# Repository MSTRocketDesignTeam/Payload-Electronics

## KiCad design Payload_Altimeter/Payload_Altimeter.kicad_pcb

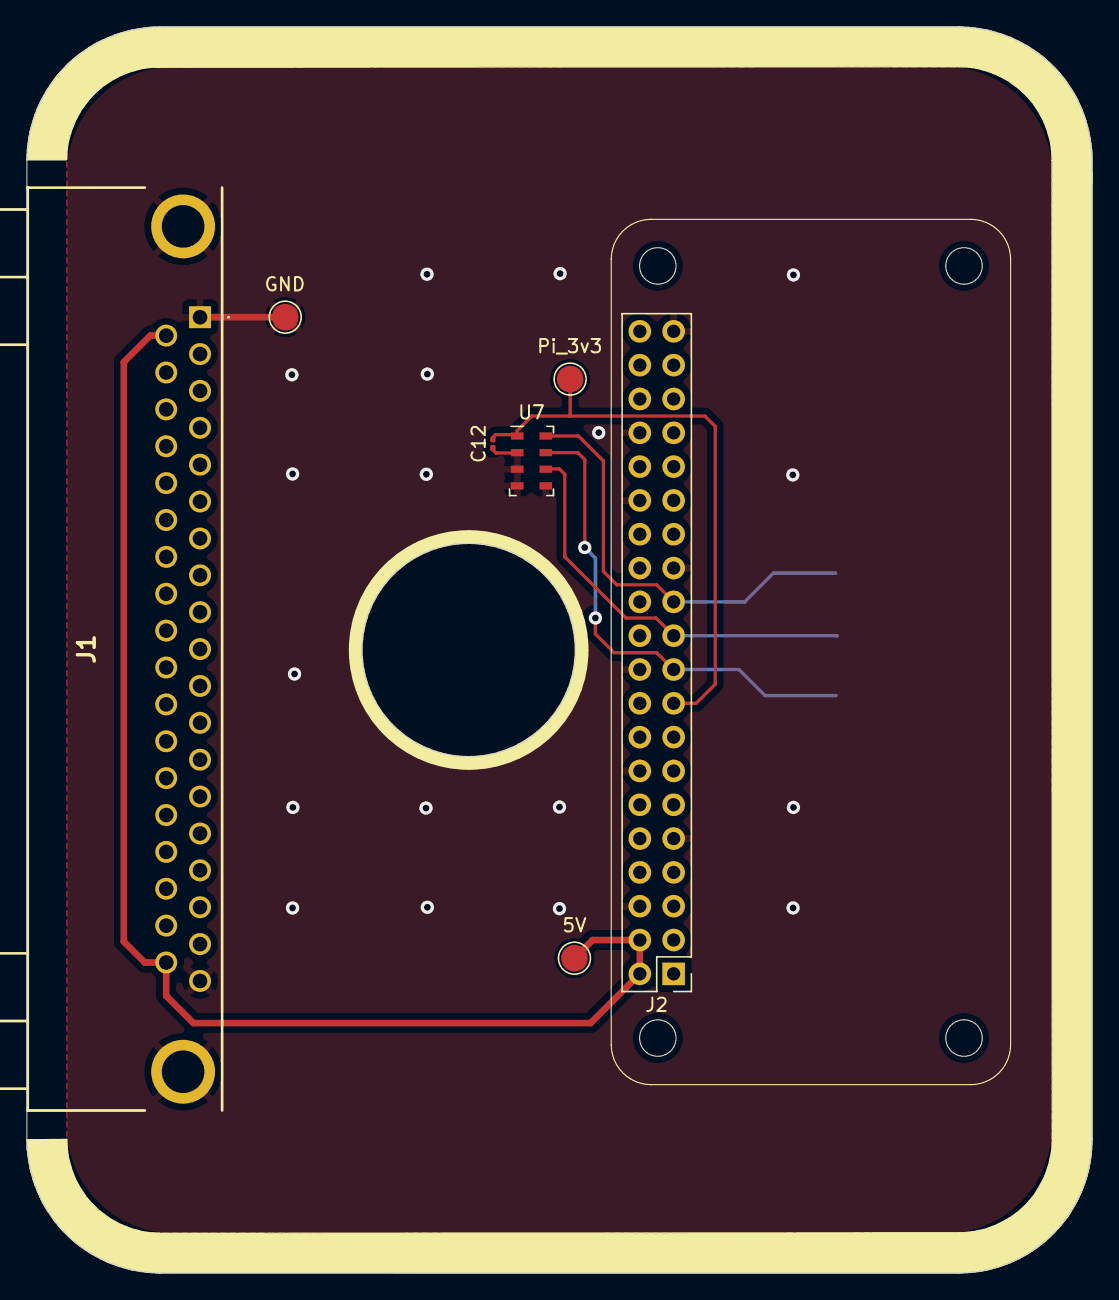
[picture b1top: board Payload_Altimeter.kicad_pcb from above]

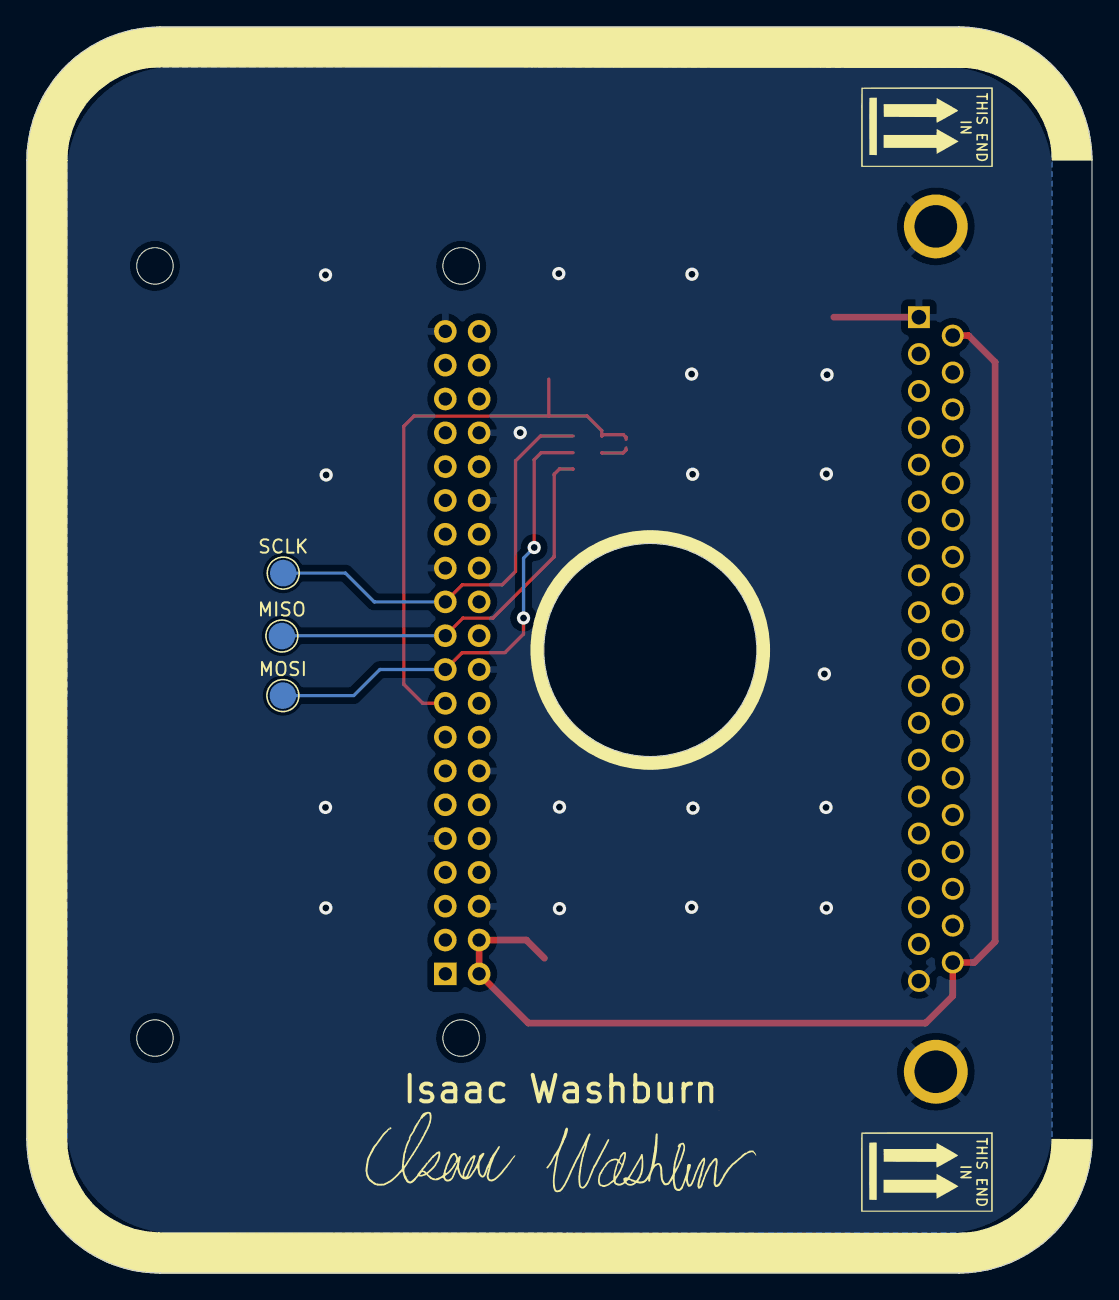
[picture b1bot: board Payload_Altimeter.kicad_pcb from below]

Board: 2 copper layers, 80.0 x 93.6 mm, 10 parts (3 on the bottom side), 7 nets.

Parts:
5V: 5V; TestPoint_Pad_D2.0mm
C12: 100nF; C_0201_0603Metric
GND: GND; TestPoint_Pad_D2.0mm
J1: L717SDC37P1ACH4F
J2: Pi_Zero; PinHeader_2x20_P2.54mm_Vertical
MISO: MISO; TestPoint_Pad_D2.0mm
MOSI: MOSI; TestPoint_Pad_D2.0mm
Pi_3v3: Pi_3v3; TestPoint_Pad_D2.0mm
SCLK: SCLK; TestPoint_Pad_D2.0mm
U7: MS5607-02BA; LGA-8_3x5mm_P1.25mm

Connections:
+3V3: J1.2, J1.18
+5V: 5V.1, J1.20, J1.37, J2.2, J2.4
/MISO: J2.21, MISO.1, U7.6 (SDO)
/MOSI: J2.19, MOSI.1, U7.7 (SDI/SDA)
/Pi_3v3: C12.1, J2.17, Pi_3v3.1, U7.1 (VDD)
/SCLK: J2.23, SCLK.1, U7.8 (SCLK)
GND: C12.2, GND.1, J1.1, J1.19, J1.MH1, J1.MH2, J2.6, J2.9, J2.14, J2.20, J2.25, J2.30, J2.34, J2.39, U7.2 (PS), U7.3 (GND), U7.4 (CSB), U7.5 (CSB)

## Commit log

2022-01-24 Added initial files
    files were added for the initial system. copied from another git so less work needed
2022-01-24 trying another git repo
    Using a different git repo for the project
2022-01-24 more changes that will be reverted
2022-01-24 changes to layout and removing old files
2022-01-24 added libraries
2022-01-24 started .pro
2022-01-24 added a bunch of stuff for the start of the board
2022-01-24 Renamed Project Folder
2022-01-24 Initialized Schematic and PCB Layout
2022-01-25 Wired 5V created Arduino Sheet
2022-01-30 added sd card
    sd card was added and traces were placed for other components
2022-01-31 Fixed wire changed capacitor
2022-02-04 Fixed Capacitor
2022-02-13 Added 3D model for Arduino Pro Mini
2022-02-14 Adjusted copper pours
2022-02-14 Adjusted center hole position
2022-02-19 Hole location changed
    Hole was moved over 2mm for tolerances
2022-02-27 Added .gitignore
2022-02-28 Corrected edge cuts, aligned center hole, adjusted silkscreen border, aligned grid, aligned all components
2022-03-07 Adjusted silkscreen
2022-03-21 Deleted SD
    Got rid of the SD card on the PCB the teensy will now be what is housing the SD card
2022-03-21 SD Card
    Got rid of SD card
2022-03-28 Added teensy footprints
    Footprints for the Teensy were added to the repo.
2022-04-25 Rasp_Pi
    Tried to put in a pi zero
2022-04-25 Finished Schematic?
2022-04-25 Some connection
    Put some of the connections on but not all of them
2022-04-28 Finished PCB Layout
2022-04-29 Added gerbs
    Gerber files were generated for PCB fabrication
2022-04-29 Gerber Files
    Additional files for the gerbs
2022-04-29 Geber ZIP
    Files were zipped and removed from mail

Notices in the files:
Payload_Altimeter/Payload_Altimeter.kicad_pcb:
License: MIT - Copyright 2018 StudioPieters®
